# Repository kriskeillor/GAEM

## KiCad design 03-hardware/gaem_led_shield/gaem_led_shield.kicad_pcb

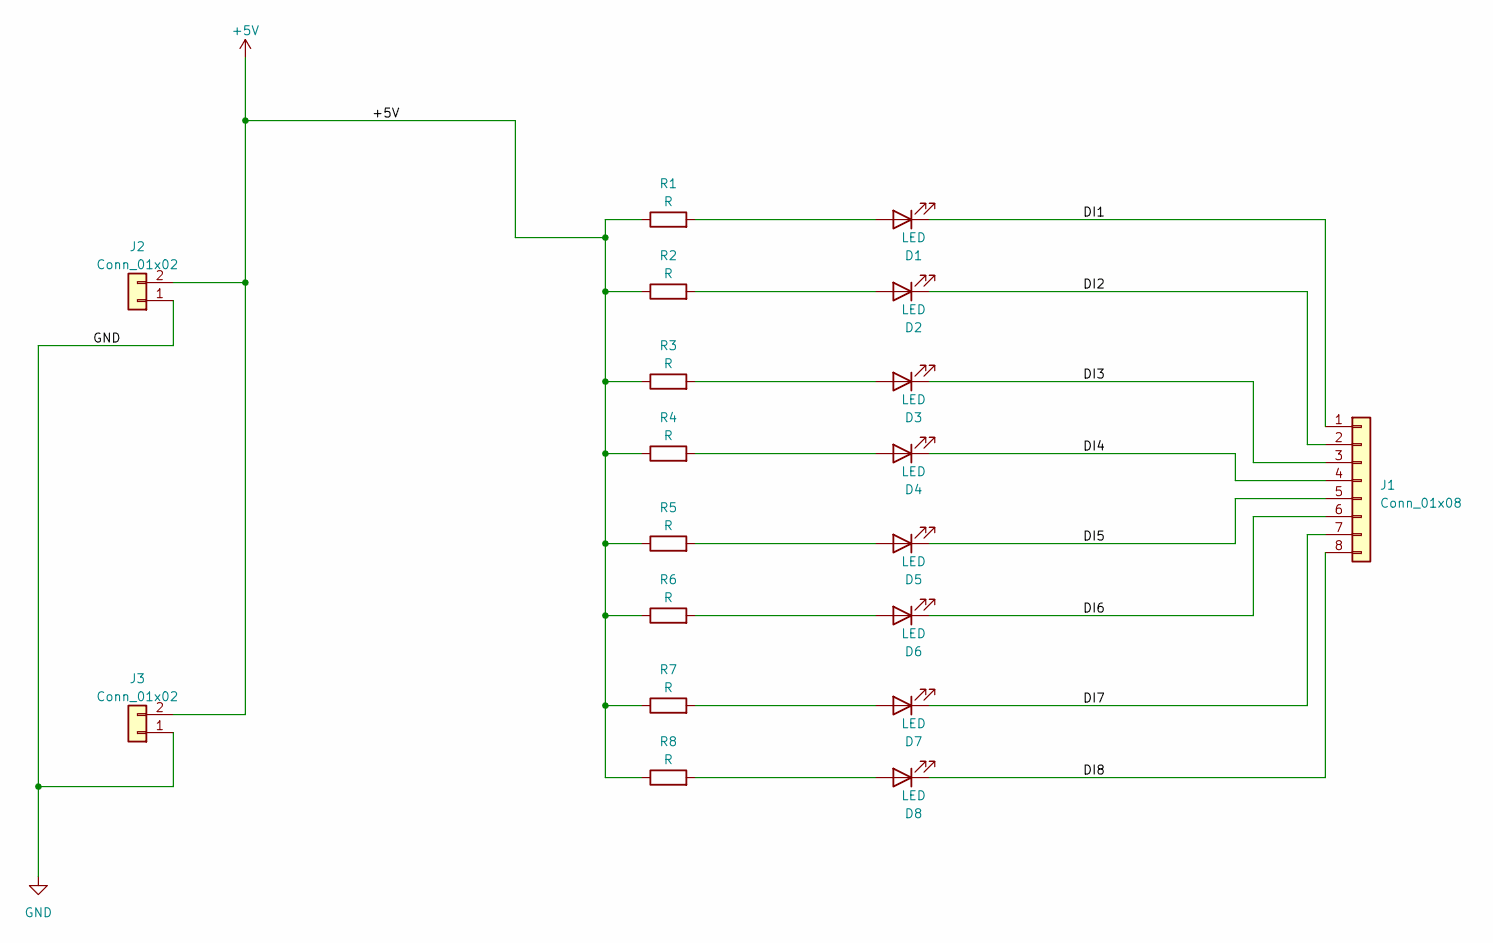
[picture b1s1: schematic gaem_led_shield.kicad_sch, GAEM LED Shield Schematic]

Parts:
D1, D2, D3, D4, D5, D6, D7, D8: LED; LED_D5.0mm
J1: Conn_01x08; PinHeader_1x08_P2.54mm_Vertical
J2, J3: Conn_01x02; PinHeader_1x02_P2.54mm_Vertical
R1, R2, R3, R4, R5, R6, R7, R8: R; R_0603_1608Metric

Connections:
+5V: J2.2, J3.2, R1.1, R2.1, R3.1, R4.1, R5.1, R6.1, R7.1, R8.1
/DI1: D1.1 (K), J1.1
/DI2: D2.1 (K), J1.2
/DI3: D3.1 (K), J1.3
/DI4: D4.1 (K), J1.4
/DI5: D5.1 (K), J1.5
/DI6: D6.1 (K), J1.6
/DI7: D7.1 (K), J1.7
/DI8: D8.1 (K), J1.8
GND: J2.1, J3.1
unnamed: D1.2 (A), R1.2
unnamed: D2.2 (A), R2.2
unnamed: D3.2 (A), R3.2
unnamed: D4.2 (A), R4.2
unnamed: D5.2 (A), R5.2
unnamed: D6.2 (A), R6.2
unnamed: D7.2 (A), R7.2
unnamed: D8.2 (A), R8.2

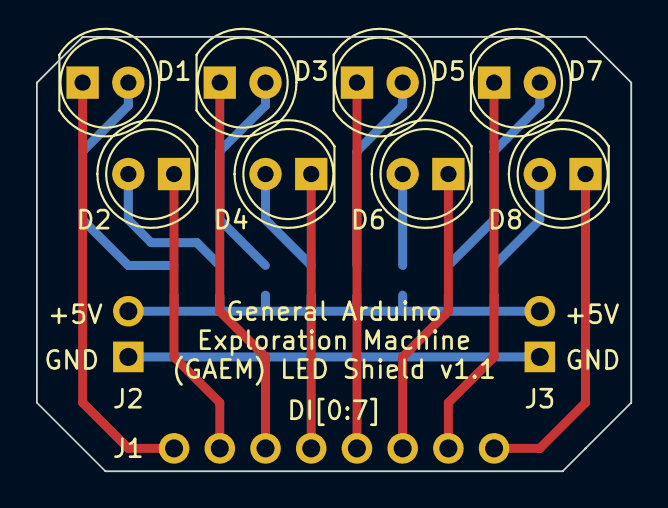
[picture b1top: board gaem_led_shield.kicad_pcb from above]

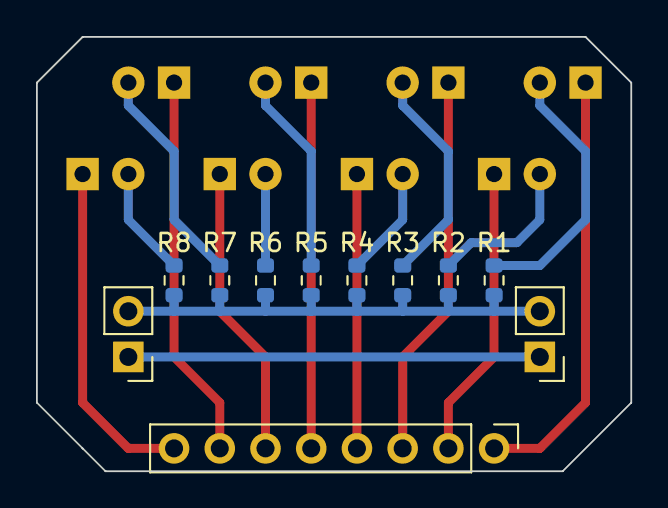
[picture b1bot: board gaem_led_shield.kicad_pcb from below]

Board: 2 copper layers, 33.0 x 24.1 mm, 19 parts (11 on the bottom side), 18 nets.

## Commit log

2023-02-04 First commit with buttons, display, and movement
2023-02-18 Reorganize code
2023-02-19 Multi file refactor, linker broken
2023-02-19 Refactor to extern keyword, deployed successfully!
2023-02-19 v1.0
2023-02-22 Rename sketch
2023-02-24 Update comment header format
2023-02-24 Add interrupt and timer for Micro but getting 0x44 error code
2023-04-28 Add soldering jig
2023-04-29 Add v1.2 soldering jig
2023-05-01 Add (fastforward) to v1.6
2023-05-01 Move arduino sketch files from root to `01-software`.
2023-05-17 rename as sketch folder and enable pullup mode for hardware revision
2025-05-29 Add v1 LED shield schematic and footprints
2025-05-29 Add LED shield v1.1 PCB layout
